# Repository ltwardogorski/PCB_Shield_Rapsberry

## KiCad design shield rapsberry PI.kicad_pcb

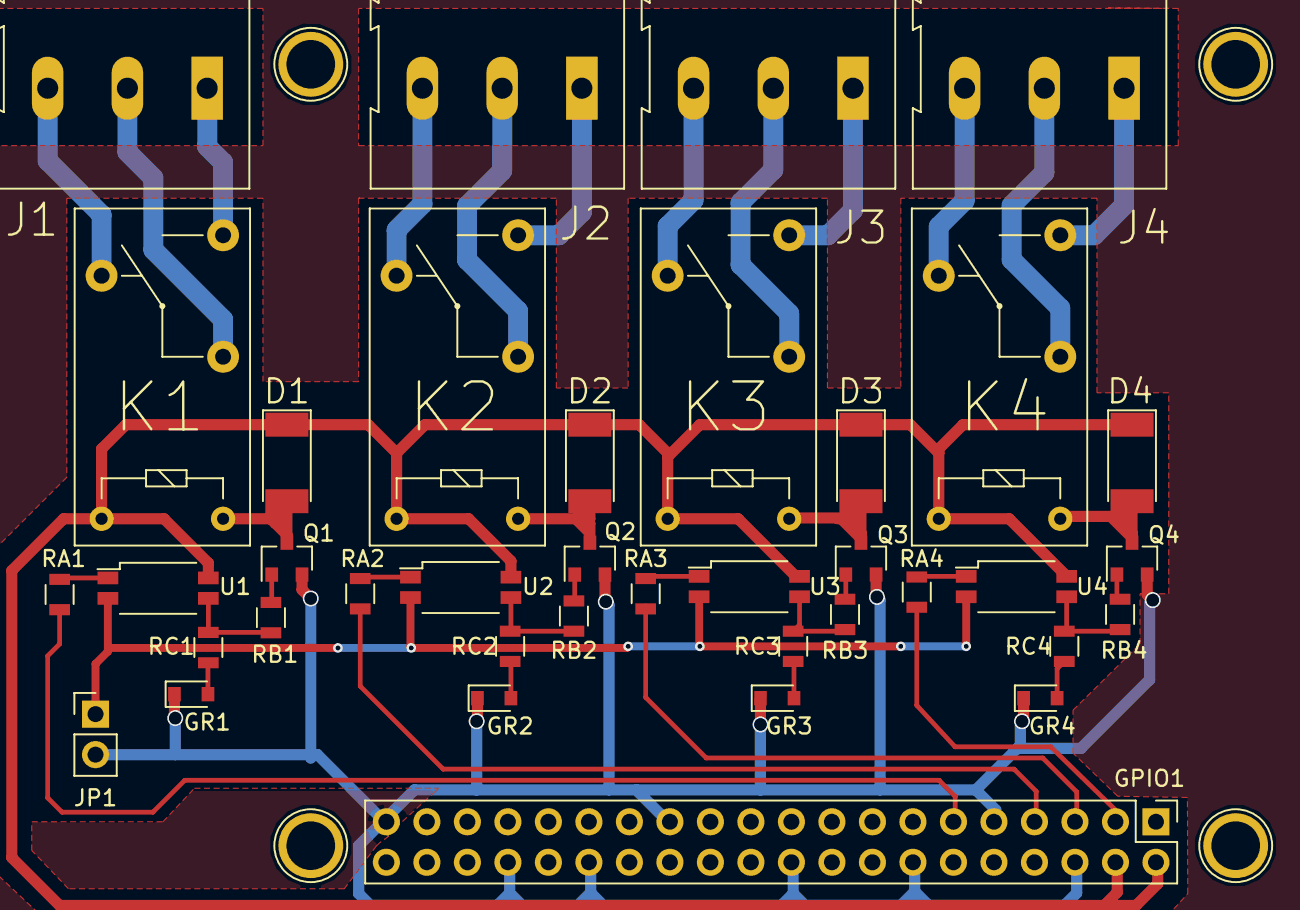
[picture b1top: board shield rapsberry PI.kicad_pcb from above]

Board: 2 copper layers, 38 parts (0 on the bottom side), 39 nets.

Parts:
D1, D2, D3, D4: SM4005; D_MELF
GPIO1: SUPP40; Pin_Header_Straight_2x20_Pitch2.54mm
GR1, GR2, GR3, GR4: GYW140; D_0805
J1, J2, J3, J4: Screw_Terminal_01x03; TerminalBlock_Altech_AK300-3_P5.00mm
JP1: Jumper GND_COM; Pin_Header_Straight_1x02_Pitch2.54mm
K1, K2, K3, K4: G5Q-1; Relay_SPDT_OMRON-G5Q
Q1, Q2, Q3, Q4: BC817; SOT-23
RA1, RA2, RA3, RA4: 180; R_0805
RB1, RB2, RB3, RB4: 470; R_0805
RC1, RC2, RC3, RC4: 180; R_0805
U1, U2, U3, U4: PC817; SOP-4_4.4x2.8mm_Pitch1.27mm

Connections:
+5V: D1.1, D2.1, D3.1, D4.1, GPIO1.2, GPIO1.4, K1.5, K2.5, K3.5, K4.5, U1.4, U2.4, U3.4, U4.4
COM: JP1.1, U1.2, U2.2, U3.2, U4.2
GND: GPIO1.6, GPIO1.9, GPIO1.14, GPIO1.20, GPIO1.25, GPIO1.30, GPIO1.34, GPIO1.39, GR1.1, GR2.1, GR3.1, GR4.1, JP1.2, Q1.2, Q2.2, Q3.2, Q4.2
IN1: J1.2, K1.2
IN2: J2.2, K2.2
IN3: J3.2, K3.2
IN4: J4.2, K4.2
NC1: J1.3, K1.4
NC2: J2.3, K2.4
NC3: J3.3, K3.4
NC4: J4.3, K4.4
NO1: J1.1, K1.3
NO2: J2.1, K2.3
NO3: J3.1, K3.3
NO4: J4.1, K4.3
unnamed: D1.2, K1.1, Q1.3
unnamed: D2.2, K2.1, Q2.3
unnamed: D3.2, K3.1, Q3.3
unnamed: D4.2, K4.1, Q4.3
unnamed: GR1.2, RC1.2
unnamed: GR2.2, RC2.2
unnamed: GR3.2, RC3.2
unnamed: GR4.2, RC4.2
unnamed: Q1.1, RB1.1
unnamed: Q2.1, RB2.2
unnamed: Q3.1, RB3.2
unnamed: Q4.1, RB4.2
unnamed: RA1.1, U1.1
unnamed: RA2.1, U2.1
unnamed: RA3.1, U3.1
unnamed: RA4.1, U4.1
unnamed: RB1.2, RC1.1, U1.3
unnamed: RB2.1, RC2.1, U2.3
unnamed: RB3.1, RC3.1, U3.3
unnamed: RB4.1, RC4.1, U4.3
OUT1: GPIO1.11, RA1.2
OUT2: GPIO1.7, RA2.2
OUT3: GPIO1.5, RA3.2
OUT4: GPIO1.3, RA4.2

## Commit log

2018-10-29 final_project
